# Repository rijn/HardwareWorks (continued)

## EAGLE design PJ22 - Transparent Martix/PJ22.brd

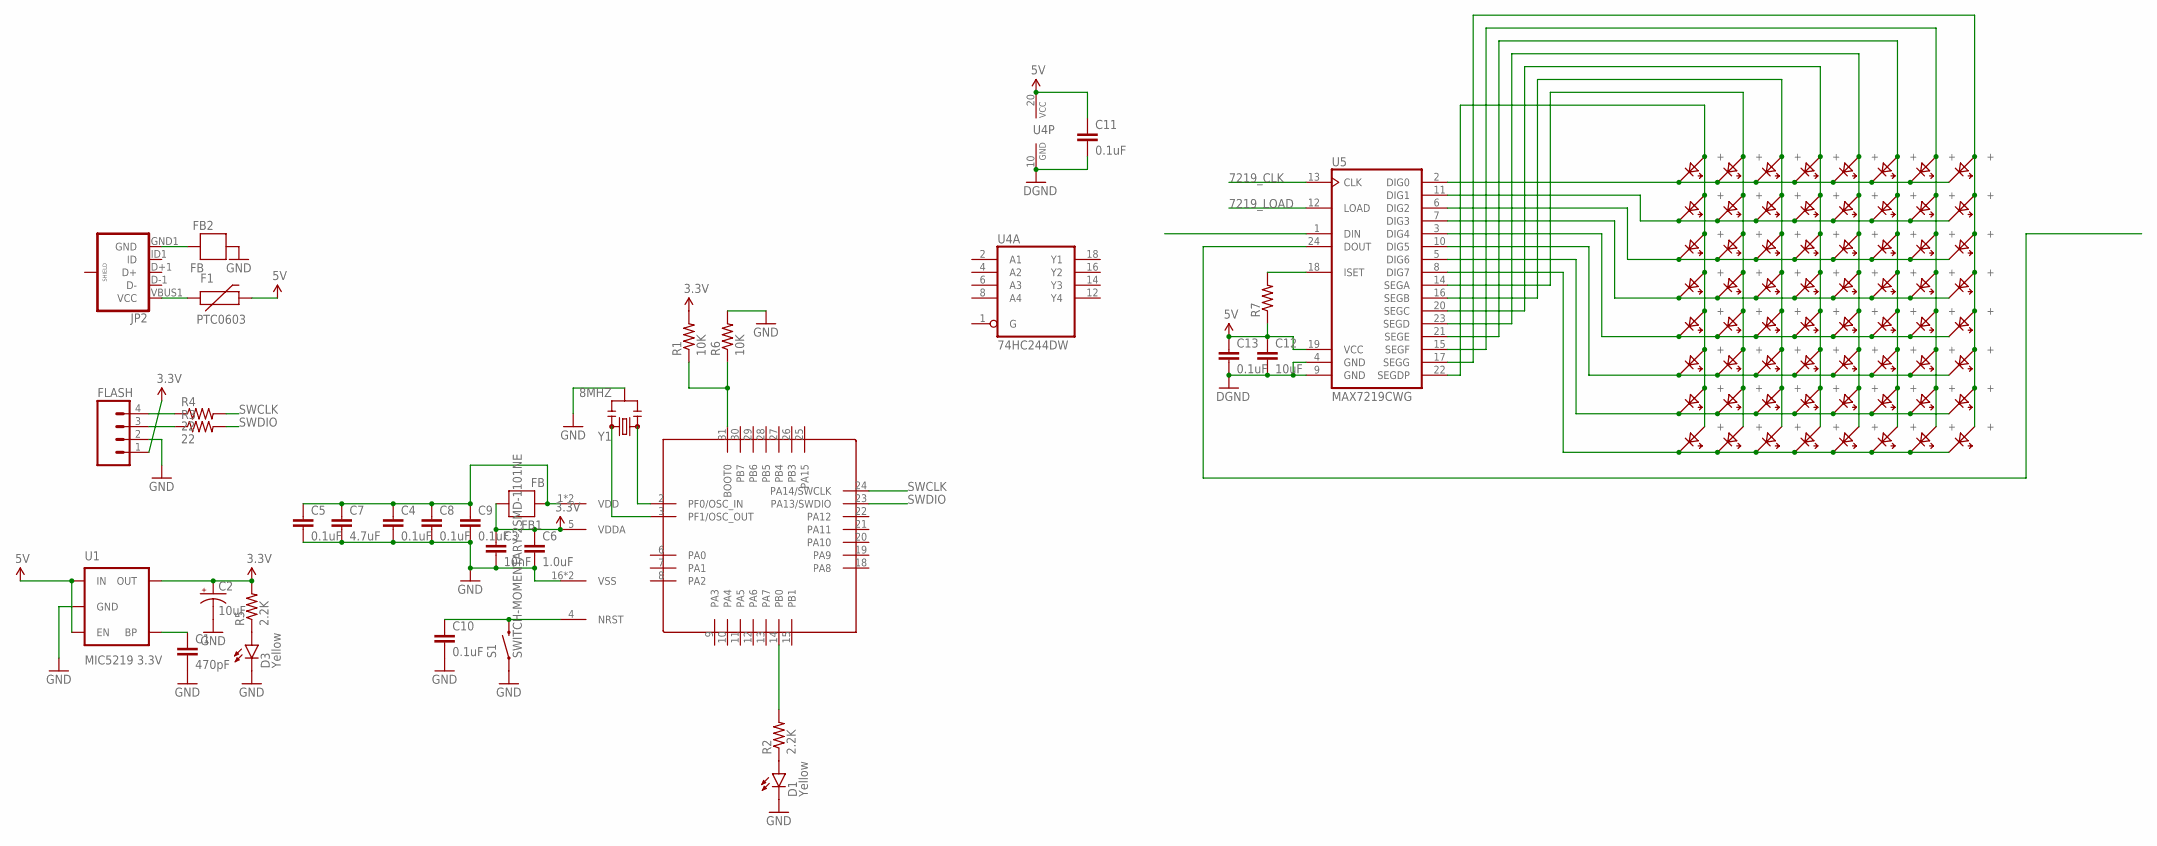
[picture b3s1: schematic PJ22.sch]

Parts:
C1: 470pF; 0402-CAP
C2: 10uF; EIA3216
C3: 10nF; 0402-CAP
C4, C5, C8, C9, C10: 0.1uF; 0402-CAP
C6: 1.0uF; 0603-CAP
C7: 4.7uF; 0603-CAP
C11, C13: 0.1uF; 0603-CAP
C12: 10uF; 1210
D1, D3: Yellow; LED-0603
DC1, DC2, DC3, DC4, DC5, DC6, DC7, DC8, DC9, DC10, DC11, DC12, DC13, DC14, DC15, DC16, DC17, DC18, DC19, DC20, DC21, DC22, DC23, DC24, DC25, DC26, DC27, DC28, DC29, DC30, DC31, DC32, DC33, DC34, DC35, DC36, DC37, DC38, DC39, DC40, DC41, DC42, DC43, DC44, DC45, DC46, DC47, DC48, DC49, DC50, DC51, DC52, DC53, DC54, DC55, DC56, DC57, DC58, DC59, DC60, DC61, DC62, DC63, DC64: LED_COMP
F1: PTC0603; 0603
FB1, FB2: FB; 0603
FLASH: M04SMD; 1X04-SMD
JP2: USB_MICROB_PLUGCONN-11752; USB-B-MICRO-SMD_V03
R1, R6: 10K; 0402-RES
R2, R5: 2.2K; 0402-RES
R3, R4: 22; 0402-RES
R7: RESISTOR0805-RES; 0805
S1: SWITCH-MOMENTARY-2SMD-1101NE; TACTILE-SWITCH-1101NE
U1: MIC5219 3.3V; SOT23-5
U2: STM32F030K6P6; LQFP32-0.8
U4: 74HC244DW; SO20W
U5: MAX7219CWG; SO24L
Y1: 8MHZ; RESONATOR-SMD

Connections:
3.3V: C2.A (+), C3.1, C6.1, FB1.1, FLASH.1, R1.2, R5.2, U1.5 (OUT), U2.5 (VDDA)
5V: C11.1, C12.1, C13.1, F1.2, R7.1, U1.1 (IN), U1.3 (EN), U4.20 (VCC), U5.19 (VCC)
7219_CLK: U5.13 (CLK)
7219_LOAD: U5.12 (LOAD)
COPOY: C1.2, C2.C (-), C3.2, C4.2, C5.2, C6.2, C7.2, C8.2, C9.2, C10.2, D1.C, D3.C, FB2.1, FLASH.2, R6.2, S1.1, U1.2 (GND), U2.16 (VSS), U2.32 (VSS), Y1.2
GND: C11.2, C12.2, C13.2, U4.10 (GND), U5.4 (GND), U5.9 (GND)
unnamed: C4.1, C5.1, C7.1, C8.1, C9.1, FB1.2, U2.1 (VDD), U2.17 (VDD)
unnamed: DC1.0603- (-), DC1.0805- (-), DC1.1206- (-), DC1.3528- (-), DC1.5050-1 (-), DC1.5050-3 (-), DC1.5050-5 (-), DC2.0603- (-), DC2.0805- (-), DC2.1206- (-), DC2.3528- (-), DC2.5050-1 (-), DC2.5050-3 (-), DC2.5050-5 (-), DC3.0603- (-), DC3.0805- (-), DC3.1206- (-), DC3.3528- (-), DC3.5050-1 (-), DC3.5050-3 (-), DC3.5050-5 (-), DC4.0603- (-), DC4.0805- (-), DC4.1206- (-), DC4.3528- (-), DC4.5050-1 (-), DC4.5050-3 (-), DC4.5050-5 (-), DC5.0603- (-), DC5.0805- (-), DC5.1206- (-), DC5.3528- (-), DC5.5050-1 (-), DC5.5050-3 (-), DC5.5050-5 (-), DC6.0603- (-), DC6.0805- (-), DC6.1206- (-), DC6.3528- (-), DC6.5050-1 (-), DC6.5050-3 (-), DC6.5050-5 (-), DC7.0603- (-), DC7.0805- (-), DC7.1206- (-), DC7.3528- (-), DC7.5050-1 (-), DC7.5050-3 (-), DC7.5050-5 (-), DC8.0603- (-), DC8.0805- (-), DC8.1206- (-), DC8.3528- (-), DC8.5050-1 (-), DC8.5050-3 (-), DC8.5050-5 (-), U5.2 (DIG0)
unnamed: C1.1, U1.4 (BP)
unnamed: FLASH.3, R3.1
unnamed: FLASH.4, R4.1
unnamed: DC9.0603- (-), DC9.0805- (-), DC9.1206- (-), DC9.3528- (-), DC9.5050-1 (-), DC9.5050-3 (-), DC9.5050-5 (-), DC10.0603- (-), DC10.0805- (-), DC10.1206- (-), DC10.3528- (-), DC10.5050-1 (-), DC10.5050-3 (-), DC10.5050-5 (-), DC11.0603- (-), DC11.0805- (-), DC11.1206- (-), DC11.3528- (-), DC11.5050-1 (-), DC11.5050-3 (-), DC11.5050-5 (-), DC12.0603- (-), DC12.0805- (-), DC12.1206- (-), DC12.3528- (-), DC12.5050-1 (-), DC12.5050-3 (-), DC12.5050-5 (-), DC13.0603- (-), DC13.0805- (-), DC13.1206- (-), DC13.3528- (-), DC13.5050-1 (-), DC13.5050-3 (-), DC13.5050-5 (-), DC14.0603- (-), DC14.0805- (-), DC14.1206- (-), DC14.3528- (-), DC14.5050-1 (-), DC14.5050-3 (-), DC14.5050-5 (-), DC15.0603- (-), DC15.0805- (-), DC15.1206- (-), DC15.3528- (-), DC15.5050-1 (-), DC15.5050-3 (-), DC15.5050-5 (-), DC16.0603- (-), DC16.0805- (-), DC16.1206- (-), DC16.3528- (-), DC16.5050-1 (-), DC16.5050-3 (-), DC16.5050-5 (-), U5.11 (DIG1)
unnamed: D1.A, R2.1
unnamed: DC1.0603+ (+), DC1.0805+ (+), DC1.1206+ (+), DC1.3528+ (+), DC1.5050-2 (+), DC1.5050-4 (+), DC1.5050-6 (+), DC9.0603+ (+), DC9.0805+ (+), DC9.1206+ (+), DC9.3528+ (+), DC9.5050-2 (+), DC9.5050-4 (+), DC9.5050-6 (+), DC17.0603+ (+), DC17.0805+ (+), DC17.1206+ (+), DC17.3528+ (+), DC17.5050-2 (+), DC17.5050-4 (+), DC17.5050-6 (+), DC25.0603+ (+), DC25.0805+ (+), DC25.1206+ (+), DC25.3528+ (+), DC25.5050-2 (+), DC25.5050-4 (+), DC25.5050-6 (+), DC33.0603+ (+), DC33.0805+ (+), DC33.1206+ (+), DC33.3528+ (+), DC33.5050-2 (+), DC33.5050-4 (+), DC33.5050-6 (+), DC41.0603+ (+), DC41.0805+ (+), DC41.1206+ (+), DC41.3528+ (+), DC41.5050-2 (+), DC41.5050-4 (+), DC41.5050-6 (+), DC49.0603+ (+), DC49.0805+ (+), DC49.1206+ (+), DC49.3528+ (+), DC49.5050-2 (+), DC49.5050-4 (+), DC49.5050-6 (+), DC57.0603+ (+), DC57.0805+ (+), DC57.1206+ (+), DC57.3528+ (+), DC57.5050-2 (+), DC57.5050-4 (+), DC57.5050-6 (+), U5.22 (SEGDP)
unnamed: R1.1, R6.1, U2.31 (BOOT0)
unnamed: DC2.0603+ (+), DC2.0805+ (+), DC2.1206+ (+), DC2.3528+ (+), DC2.5050-2 (+), DC2.5050-4 (+), DC2.5050-6 (+), DC10.0603+ (+), DC10.0805+ (+), DC10.1206+ (+), DC10.3528+ (+), DC10.5050-2 (+), DC10.5050-4 (+), DC10.5050-6 (+), DC18.0603+ (+), DC18.0805+ (+), DC18.1206+ (+), DC18.3528+ (+), DC18.5050-2 (+), DC18.5050-4 (+), DC18.5050-6 (+), DC26.0603+ (+), DC26.0805+ (+), DC26.1206+ (+), DC26.3528+ (+), DC26.5050-2 (+), DC26.5050-4 (+), DC26.5050-6 (+), DC34.0603+ (+), DC34.0805+ (+), DC34.1206+ (+), DC34.3528+ (+), DC34.5050-2 (+), DC34.5050-4 (+), DC34.5050-6 (+), DC42.0603+ (+), DC42.0805+ (+), DC42.1206+ (+), DC42.3528+ (+), DC42.5050-2 (+), DC42.5050-4 (+), DC42.5050-6 (+), DC50.0603+ (+), DC50.0805+ (+), DC50.1206+ (+), DC50.3528+ (+), DC50.5050-2 (+), DC50.5050-4 (+), DC50.5050-6 (+), DC58.0603+ (+), DC58.0805+ (+), DC58.1206+ (+), DC58.3528+ (+), DC58.5050-2 (+), DC58.5050-4 (+), DC58.5050-6 (+), U5.14 (SEGA)
unnamed: FB2.2, JP2.GND1 (GND)
unnamed: F1.1, JP2.VBUS1 (VCC)
unnamed: DC3.0603+ (+), DC3.0805+ (+), DC3.1206+ (+), DC3.3528+ (+), DC3.5050-2 (+), DC3.5050-4 (+), DC3.5050-6 (+), DC11.0603+ (+), DC11.0805+ (+), DC11.1206+ (+), DC11.3528+ (+), DC11.5050-2 (+), DC11.5050-4 (+), DC11.5050-6 (+), DC19.0603+ (+), DC19.0805+ (+), DC19.1206+ (+), DC19.3528+ (+), DC19.5050-2 (+), DC19.5050-4 (+), DC19.5050-6 (+), DC27.0603+ (+), DC27.0805+ (+), DC27.1206+ (+), DC27.3528+ (+), DC27.5050-2 (+), DC27.5050-4 (+), DC27.5050-6 (+), DC35.0603+ (+), DC35.0805+ (+), DC35.1206+ (+), DC35.3528+ (+), DC35.5050-2 (+), DC35.5050-4 (+), DC35.5050-6 (+), DC43.0603+ (+), DC43.0805+ (+), DC43.1206+ (+), DC43.3528+ (+), DC43.5050-2 (+), DC43.5050-4 (+), DC43.5050-6 (+), DC51.0603+ (+), DC51.0805+ (+), DC51.1206+ (+), DC51.3528+ (+), DC51.5050-2 (+), DC51.5050-4 (+), DC51.5050-6 (+), DC59.0603+ (+), DC59.0805+ (+), DC59.1206+ (+), DC59.3528+ (+), DC59.5050-2 (+), DC59.5050-4 (+), DC59.5050-6 (+), U5.16 (SEGB)
unnamed: DC4.0603+ (+), DC4.0805+ (+), DC4.1206+ (+), DC4.3528+ (+), DC4.5050-2 (+), DC4.5050-4 (+), DC4.5050-6 (+), DC12.0603+ (+), DC12.0805+ (+), DC12.1206+ (+), DC12.3528+ (+), DC12.5050-2 (+), DC12.5050-4 (+), DC12.5050-6 (+), DC20.0603+ (+), DC20.0805+ (+), DC20.1206+ (+), DC20.3528+ (+), DC20.5050-2 (+), DC20.5050-4 (+), DC20.5050-6 (+), DC28.0603+ (+), DC28.0805+ (+), DC28.1206+ (+), DC28.3528+ (+), DC28.5050-2 (+), DC28.5050-4 (+), DC28.5050-6 (+), DC36.0603+ (+), DC36.0805+ (+), DC36.1206+ (+), DC36.3528+ (+), DC36.5050-2 (+), DC36.5050-4 (+), DC36.5050-6 (+), DC44.0603+ (+), DC44.0805+ (+), DC44.1206+ (+), DC44.3528+ (+), DC44.5050-2 (+), DC44.5050-4 (+), DC44.5050-6 (+), DC52.0603+ (+), DC52.0805+ (+), DC52.1206+ (+), DC52.3528+ (+), DC52.5050-2 (+), DC52.5050-4 (+), DC52.5050-6 (+), DC60.0603+ (+), DC60.0805+ (+), DC60.1206+ (+), DC60.3528+ (+), DC60.5050-2 (+), DC60.5050-4 (+), DC60.5050-6 (+), U5.20 (SEGC)
unnamed: DC5.0603+ (+), DC5.0805+ (+), DC5.1206+ (+), DC5.3528+ (+), DC5.5050-2 (+), DC5.5050-4 (+), DC5.5050-6 (+), DC13.0603+ (+), DC13.0805+ (+), DC13.1206+ (+), DC13.3528+ (+), DC13.5050-2 (+), DC13.5050-4 (+), DC13.5050-6 (+), DC21.0603+ (+), DC21.0805+ (+), DC21.1206+ (+), DC21.3528+ (+), DC21.5050-2 (+), DC21.5050-4 (+), DC21.5050-6 (+), DC29.0603+ (+), DC29.0805+ (+), DC29.1206+ (+), DC29.3528+ (+), DC29.5050-2 (+), DC29.5050-4 (+), DC29.5050-6 (+), DC37.0603+ (+), DC37.0805+ (+), DC37.1206+ (+), DC37.3528+ (+), DC37.5050-2 (+), DC37.5050-4 (+), DC37.5050-6 (+), DC45.0603+ (+), DC45.0805+ (+), DC45.1206+ (+), DC45.3528+ (+), DC45.5050-2 (+), DC45.5050-4 (+), DC45.5050-6 (+), DC53.0603+ (+), DC53.0805+ (+), DC53.1206+ (+), DC53.3528+ (+), DC53.5050-2 (+), DC53.5050-4 (+), DC53.5050-6 (+), DC61.0603+ (+), DC61.0805+ (+), DC61.1206+ (+), DC61.3528+ (+), DC61.5050-2 (+), DC61.5050-4 (+), DC61.5050-6 (+), U5.23 (SEGD)
unnamed: DC6.0603+ (+), DC6.0805+ (+), DC6.1206+ (+), DC6.3528+ (+), DC6.5050-2 (+), DC6.5050-4 (+), DC6.5050-6 (+), DC14.0603+ (+), DC14.0805+ (+), DC14.1206+ (+), DC14.3528+ (+), DC14.5050-2 (+), DC14.5050-4 (+), DC14.5050-6 (+), DC22.0603+ (+), DC22.0805+ (+), DC22.1206+ (+), DC22.3528+ (+), DC22.5050-2 (+), DC22.5050-4 (+), DC22.5050-6 (+), DC30.0603+ (+), DC30.0805+ (+), DC30.1206+ (+), DC30.3528+ (+), DC30.5050-2 (+), DC30.5050-4 (+), DC30.5050-6 (+), DC38.0603+ (+), DC38.0805+ (+), DC38.1206+ (+), DC38.3528+ (+), DC38.5050-2 (+), DC38.5050-4 (+), DC38.5050-6 (+), DC46.0603+ (+), DC46.0805+ (+), DC46.1206+ (+), DC46.3528+ (+), DC46.5050-2 (+), DC46.5050-4 (+), DC46.5050-6 (+), DC54.0603+ (+), DC54.0805+ (+), DC54.1206+ (+), DC54.3528+ (+), DC54.5050-2 (+), DC54.5050-4 (+), DC54.5050-6 (+), DC62.0603+ (+), DC62.0805+ (+), DC62.1206+ (+), DC62.3528+ (+), DC62.5050-2 (+), DC62.5050-4 (+), DC62.5050-6 (+), U5.21 (SEGE)
unnamed: DC7.0603+ (+), DC7.0805+ (+), DC7.1206+ (+), DC7.3528+ (+), DC7.5050-2 (+), DC7.5050-4 (+), DC7.5050-6 (+), DC15.0603+ (+), DC15.0805+ (+), DC15.1206+ (+), DC15.3528+ (+), DC15.5050-2 (+), DC15.5050-4 (+), DC15.5050-6 (+), DC23.0603+ (+), DC23.0805+ (+), DC23.1206+ (+), DC23.3528+ (+), DC23.5050-2 (+), DC23.5050-4 (+), DC23.5050-6 (+), DC31.0603+ (+), DC31.0805+ (+), DC31.1206+ (+), DC31.3528+ (+), DC31.5050-2 (+), DC31.5050-4 (+), DC31.5050-6 (+), DC39.0603+ (+), DC39.0805+ (+), DC39.1206+ (+), DC39.3528+ (+), DC39.5050-2 (+), DC39.5050-4 (+), DC39.5050-6 (+), DC47.0603+ (+), DC47.0805+ (+), DC47.1206+ (+), DC47.3528+ (+), DC47.5050-2 (+), DC47.5050-4 (+), DC47.5050-6 (+), DC55.0603+ (+), DC55.0805+ (+), DC55.1206+ (+), DC55.3528+ (+), DC55.5050-2 (+), DC55.5050-4 (+), DC55.5050-6 (+), DC63.0603+ (+), DC63.0805+ (+), DC63.1206+ (+), DC63.3528+ (+), DC63.5050-2 (+), DC63.5050-4 (+), DC63.5050-6 (+), U5.15 (SEGF)
unnamed: DC8.0603+ (+), DC8.0805+ (+), DC8.1206+ (+), DC8.3528+ (+), DC8.5050-2 (+), DC8.5050-4 (+), DC8.5050-6 (+), DC16.0603+ (+), DC16.0805+ (+), DC16.1206+ (+), DC16.3528+ (+), DC16.5050-2 (+), DC16.5050-4 (+), DC16.5050-6 (+), DC24.0603+ (+), DC24.0805+ (+), DC24.1206+ (+), DC24.3528+ (+), DC24.5050-2 (+), DC24.5050-4 (+), DC24.5050-6 (+), DC32.0603+ (+), DC32.0805+ (+), DC32.1206+ (+), DC32.3528+ (+), DC32.5050-2 (+), DC32.5050-4 (+), DC32.5050-6 (+), DC40.0603+ (+), DC40.0805+ (+), DC40.1206+ (+), DC40.3528+ (+), DC40.5050-2 (+), DC40.5050-4 (+), DC40.5050-6 (+), DC48.0603+ (+), DC48.0805+ (+), DC48.1206+ (+), DC48.3528+ (+), DC48.5050-2 (+), DC48.5050-4 (+), DC48.5050-6 (+), DC56.0603+ (+), DC56.0805+ (+), DC56.1206+ (+), DC56.3528+ (+), DC56.5050-2 (+), DC56.5050-4 (+), DC56.5050-6 (+), DC64.0603+ (+), DC64.0805+ (+), DC64.1206+ (+), DC64.3528+ (+), DC64.5050-2 (+), DC64.5050-4 (+), DC64.5050-6 (+), U5.17 (SEGG)
unnamed: DC17.0603- (-), DC17.0805- (-), DC17.1206- (-), DC17.3528- (-), DC17.5050-1 (-), DC17.5050-3 (-), DC17.5050-5 (-), DC18.0603- (-), DC18.0805- (-), DC18.1206- (-), DC18.3528- (-), DC18.5050-1 (-), DC18.5050-3 (-), DC18.5050-5 (-), DC19.0603- (-), DC19.0805- (-), DC19.1206- (-), DC19.3528- (-), DC19.5050-1 (-), DC19.5050-3 (-), DC19.5050-5 (-), DC20.0603- (-), DC20.0805- (-), DC20.1206- (-), DC20.3528- (-), DC20.5050-1 (-), DC20.5050-3 (-), DC20.5050-5 (-), DC21.0603- (-), DC21.0805- (-), DC21.1206- (-), DC21.3528- (-), DC21.5050-1 (-), DC21.5050-3 (-), DC21.5050-5 (-), DC22.0603- (-), DC22.0805- (-), DC22.1206- (-), DC22.3528- (-), DC22.5050-1 (-), DC22.5050-3 (-), DC22.5050-5 (-), DC23.0603- (-), DC23.0805- (-), DC23.1206- (-), DC23.3528- (-), DC23.5050-1 (-), DC23.5050-3 (-), DC23.5050-5 (-), DC24.0603- (-), DC24.0805- (-), DC24.1206- (-), DC24.3528- (-), DC24.5050-1 (-), DC24.5050-3 (-), DC24.5050-5 (-), U5.6 (DIG2)
unnamed: DC25.0603- (-), DC25.0805- (-), DC25.1206- (-), DC25.3528- (-), DC25.5050-1 (-), DC25.5050-3 (-), DC25.5050-5 (-), DC26.0603- (-), DC26.0805- (-), DC26.1206- (-), DC26.3528- (-), DC26.5050-1 (-), DC26.5050-3 (-), DC26.5050-5 (-), DC27.0603- (-), DC27.0805- (-), DC27.1206- (-), DC27.3528- (-), DC27.5050-1 (-), DC27.5050-3 (-), DC27.5050-5 (-), DC28.0603- (-), DC28.0805- (-), DC28.1206- (-), DC28.3528- (-), DC28.5050-1 (-), DC28.5050-3 (-), DC28.5050-5 (-), DC29.0603- (-), DC29.0805- (-), DC29.1206- (-), DC29.3528- (-), DC29.5050-1 (-), DC29.5050-3 (-), DC29.5050-5 (-), DC30.0603- (-), DC30.0805- (-), DC30.1206- (-), DC30.3528- (-), DC30.5050-1 (-), DC30.5050-3 (-), DC30.5050-5 (-), DC31.0603- (-), DC31.0805- (-), DC31.1206- (-), DC31.3528- (-), DC31.5050-1 (-), DC31.5050-3 (-), DC31.5050-5 (-), DC32.0603- (-), DC32.0805- (-), DC32.1206- (-), DC32.3528- (-), DC32.5050-1 (-), DC32.5050-3 (-), DC32.5050-5 (-), U5.7 (DIG3)
unnamed: DC33.0603- (-), DC33.0805- (-), DC33.1206- (-), DC33.3528- (-), DC33.5050-1 (-), DC33.5050-3 (-), DC33.5050-5 (-), DC34.0603- (-), DC34.0805- (-), DC34.1206- (-), DC34.3528- (-), DC34.5050-1 (-), DC34.5050-3 (-), DC34.5050-5 (-), DC35.0603- (-), DC35.0805- (-), DC35.1206- (-), DC35.3528- (-), DC35.5050-1 (-), DC35.5050-3 (-), DC35.5050-5 (-), DC36.0603- (-), DC36.0805- (-), DC36.1206- (-), DC36.3528- (-), DC36.5050-1 (-), DC36.5050-3 (-), DC36.5050-5 (-), DC37.0603- (-), DC37.0805- (-), DC37.1206- (-), DC37.3528- (-), DC37.5050-1 (-), DC37.5050-3 (-), DC37.5050-5 (-), DC38.0603- (-), DC38.0805- (-), DC38.1206- (-), DC38.3528- (-), DC38.5050-1 (-), DC38.5050-3 (-), DC38.5050-5 (-), DC39.0603- (-), DC39.0805- (-), DC39.1206- (-), DC39.3528- (-), DC39.5050-1 (-), DC39.5050-3 (-), DC39.5050-5 (-), DC40.0603- (-), DC40.0805- (-), DC40.1206- (-), DC40.3528- (-), DC40.5050-1 (-), DC40.5050-3 (-), DC40.5050-5 (-), U5.3 (DIG4)
unnamed: DC41.0603- (-), DC41.0805- (-), DC41.1206- (-), DC41.3528- (-), DC41.5050-1 (-), DC41.5050-3 (-), DC41.5050-5 (-), DC42.0603- (-), DC42.0805- (-), DC42.1206- (-), DC42.3528- (-), DC42.5050-1 (-), DC42.5050-3 (-), DC42.5050-5 (-), DC43.0603- (-), DC43.0805- (-), DC43.1206- (-), DC43.3528- (-), DC43.5050-1 (-), DC43.5050-3 (-), DC43.5050-5 (-), DC44.0603- (-), DC44.0805- (-), DC44.1206- (-), DC44.3528- (-), DC44.5050-1 (-), DC44.5050-3 (-), DC44.5050-5 (-), DC45.0603- (-), DC45.0805- (-), DC45.1206- (-), DC45.3528- (-), DC45.5050-1 (-), DC45.5050-3 (-), DC45.5050-5 (-), DC46.0603- (-), DC46.0805- (-), DC46.1206- (-), DC46.3528- (-), DC46.5050-1 (-), DC46.5050-3 (-), DC46.5050-5 (-), DC47.0603- (-), DC47.0805- (-), DC47.1206- (-), DC47.3528- (-), DC47.5050-1 (-), DC47.5050-3 (-), DC47.5050-5 (-), DC48.0603- (-), DC48.0805- (-), DC48.1206- (-), DC48.3528- (-), DC48.5050-1 (-), DC48.5050-3 (-), DC48.5050-5 (-), U5.10 (DIG5)
unnamed: DC49.0603- (-), DC49.0805- (-), DC49.1206- (-), DC49.3528- (-), DC49.5050-1 (-), DC49.5050-3 (-), DC49.5050-5 (-), DC50.0603- (-), DC50.0805- (-), DC50.1206- (-), DC50.3528- (-), DC50.5050-1 (-), DC50.5050-3 (-), DC50.5050-5 (-), DC51.0603- (-), DC51.0805- (-), DC51.1206- (-), DC51.3528- (-), DC51.5050-1 (-), DC51.5050-3 (-), DC51.5050-5 (-), DC52.0603- (-), DC52.0805- (-), DC52.1206- (-), DC52.3528- (-), DC52.5050-1 (-), DC52.5050-3 (-), DC52.5050-5 (-), DC53.0603- (-), DC53.0805- (-), DC53.1206- (-), DC53.3528- (-), DC53.5050-1 (-), DC53.5050-3 (-), DC53.5050-5 (-), DC54.0603- (-), DC54.0805- (-), DC54.1206- (-), DC54.3528- (-), DC54.5050-1 (-), DC54.5050-3 (-), DC54.5050-5 (-), DC55.0603- (-), DC55.0805- (-), DC55.1206- (-), DC55.3528- (-), DC55.5050-1 (-), DC55.5050-3 (-), DC55.5050-5 (-), DC56.0603- (-), DC56.0805- (-), DC56.1206- (-), DC56.3528- (-), DC56.5050-1 (-), DC56.5050-3 (-), DC56.5050-5 (-), U5.5 (DIG6)
unnamed: DC57.0603- (-), DC57.0805- (-), DC57.1206- (-), DC57.3528- (-), DC57.5050-1 (-), DC57.5050-3 (-), DC57.5050-5 (-), DC58.0603- (-), DC58.0805- (-), DC58.1206- (-), DC58.3528- (-), DC58.5050-1 (-), DC58.5050-3 (-), DC58.5050-5 (-), DC59.0603- (-), DC59.0805- (-), DC59.1206- (-), DC59.3528- (-), DC59.5050-1 (-), DC59.5050-3 (-), DC59.5050-5 (-), DC60.0603- (-), DC60.0805- (-), DC60.1206- (-), DC60.3528- (-), DC60.5050-1 (-), DC60.5050-3 (-), DC60.5050-5 (-), DC61.0603- (-), DC61.0805- (-), DC61.1206- (-), DC61.3528- (-), DC61.5050-1 (-), DC61.5050-3 (-), DC61.5050-5 (-), DC62.0603- (-), DC62.0805- (-), DC62.1206- (-), DC62.3528- (-), DC62.5050-1 (-), DC62.5050-3 (-), DC62.5050-5 (-), DC63.0603- (-), DC63.0805- (-), DC63.1206- (-), DC63.3528- (-), DC63.5050-1 (-), DC63.5050-3 (-), DC63.5050-5 (-), DC64.0603- (-), DC64.0805- (-), DC64.1206- (-), DC64.3528- (-), DC64.5050-1 (-), DC64.5050-3 (-), DC64.5050-5 (-), U5.8 (DIG7)
unnamed: R7.2, U5.18 (ISET)
unnamed: D3.A, R5.1
NRST: C10.1, S1.2, U2.4 (NRST)
PB0: R2.2, U2.14 (PB0)
PF0: U2.2 (PF0/OSC_IN), Y1.1
PF1: U2.3 (PF1/OSC_OUT), Y1.3
SWCLK: R4.2, U2.24 (PA14/SWCLK)
SWDIO: R3.2, U2.23 (PA13/SWDIO)

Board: 2 copper layers, 97 parts (0 on the bottom side), 36 nets, no tracks yet.

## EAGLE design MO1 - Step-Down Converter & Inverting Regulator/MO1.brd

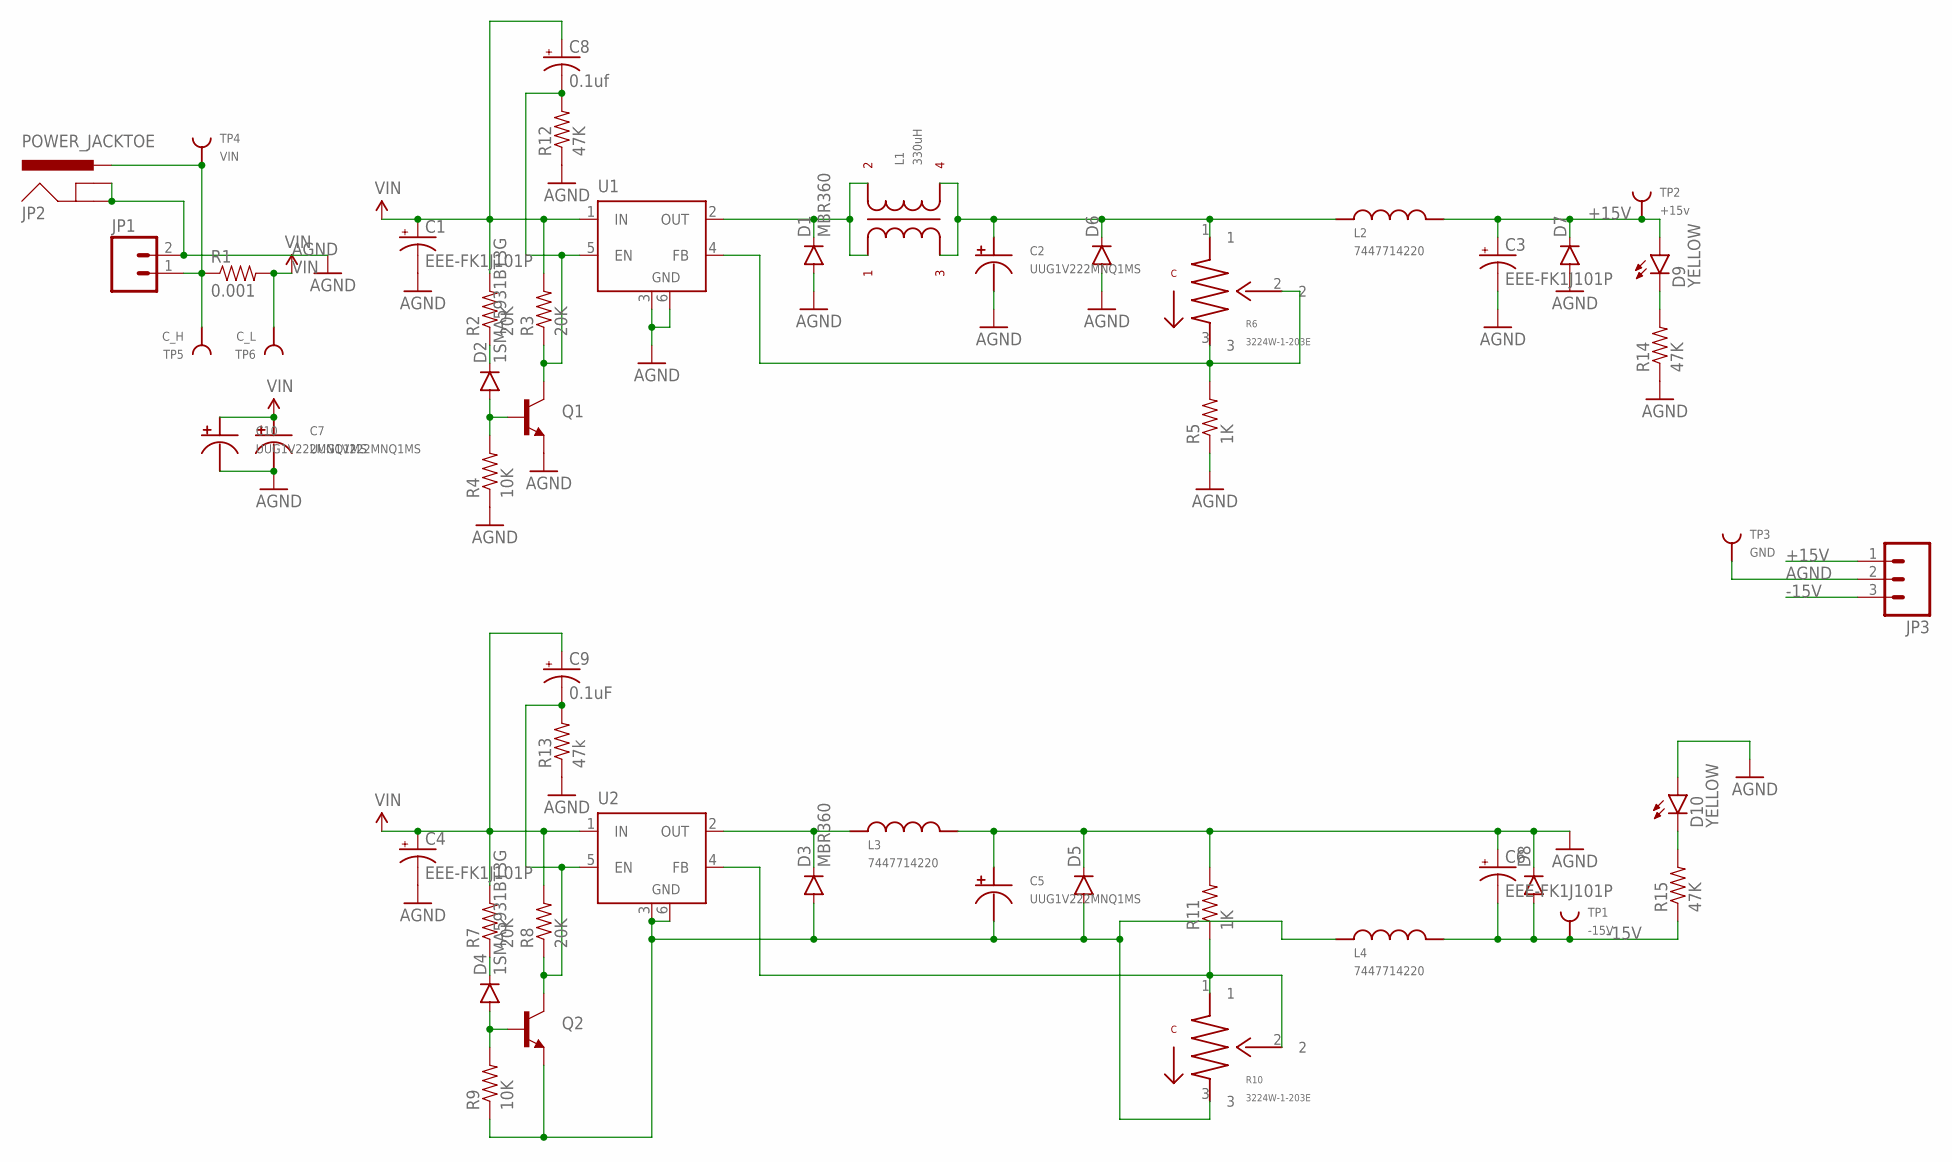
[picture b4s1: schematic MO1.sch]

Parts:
C1, C3, C4, C6: EEE-FK1J101P; PANASONIC_G
C2, C5, C7, C10: UUG1V222MNQ1MS; POL_18X21.5
C8: 0.1uf; PANASONIC_C
C9: 0.1uF; PANASONIC_C
D1, D3: MBR360; SMB-DIODE
D2, D4: 1SMA5931BT3G; SMA-DIODE
D5, D6, D7, D8: DIODESMA; SMA-DIODE
D9, D10: YELLOW; LED-1206
JP1: M023.5MM_LOCK; SCREWTERMINAL-3.5MM-2_LOCK
JP2: POWER_JACKTOE; POWER_JACK_SMD_OVERPASTE_TOE
JP3: M03SCREW_LOCK; SCREWTERMINAL-3.5MM-3_LOCK.007S
L1: 330uH; DRQ127
L2, L3, L4: 7447714220; INDUCTOR_10X10
Q1, Q2: TRANSISTOR_NPNSOT23-3; SOT23-3
R1: 0.001; 2512
R2, R3, R7, R8: 20K; 0603-RES
R4, R9: 10K; 0603-RES
R5, R11: 1K; 0805
R6, R10: 3224W-1-203E; 3224W
R12, R14, R15: 47K; 0603-RES
R13: 47k; 0603-RES
TP1: -15V; TP
TP2: +15v; TP
TP3: GND; TP
TP4: VIN; TP
TP5: C_H; TP
TP6: C_L; TP
U1, U2: LM2596S; TO263-5

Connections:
+15V: C3.+, D7.C, D9.A, JP3.1, L2.2, TP2.P$1
-15V: C6.-, D8.A, JP3.3, L4.2, R15.1, TP1.P$1
AGND: C1.-, C2.NEGATIVE, C3.-, C4.-, C5.POSITIVE, C6.+, C7.NEGATIVE, C10.NEGATIVE, D1.A, D5.C, D6.A, D7.A, D8.C, D10.A, JP1.2, JP2.GND (GNDBREAK), JP2.P$4 (GND), JP3.2, L3.2, Q1.2 (E), R4.1, R5.1, R11.2, R12.1, R13.1, R14.1, TP3.P$1, U1.3 (GND), U1.6 (GND)
unnamed: JP1.1, JP2.VIN0 (PWR), R1.1, TP4.P$1, TP5.P$1
unnamed: C2.POSITIVE, D6.C, L1.3, L1.4, L2.1, R6.1
unnamed: D1.C, L1.1, L1.2, U1.2 (OUT)
unnamed: D2.C, R2.1
unnamed: D2.A, Q1.1 (B), R4.2
unnamed: D9.C, R14.2
unnamed: R5.2, R6.2, R6.3, U1.4 (FB)
unnamed: D3.C, L3.1, U2.2 (OUT)
unnamed: C5.NEGATIVE, D3.A, D5.A, L4.1, Q2.2 (E), R9.1, R10.3, U2.3 (GND), U2.6 (GND)
unnamed: D4.C, R7.1
unnamed: D4.A, Q2.1 (B), R9.2
unnamed: D10.C, R15.2
unnamed: R10.1, R10.2, R11.1, U2.4 (FB)
unnamed: C8.-, Q1.3 (C), R3.1, R12.2, U1.5 (EN)
unnamed: C9.-, Q2.3 (C), R8.1, R13.2, U2.5 (EN)
VIN: C1.+, C4.+, C7.POSITIVE, C8.+, C9.+, C10.POSITIVE, R1.2, R2.2, R3.2, R7.2, R8.2, TP6.P$1, U1.1 (IN), U2.1 (IN)

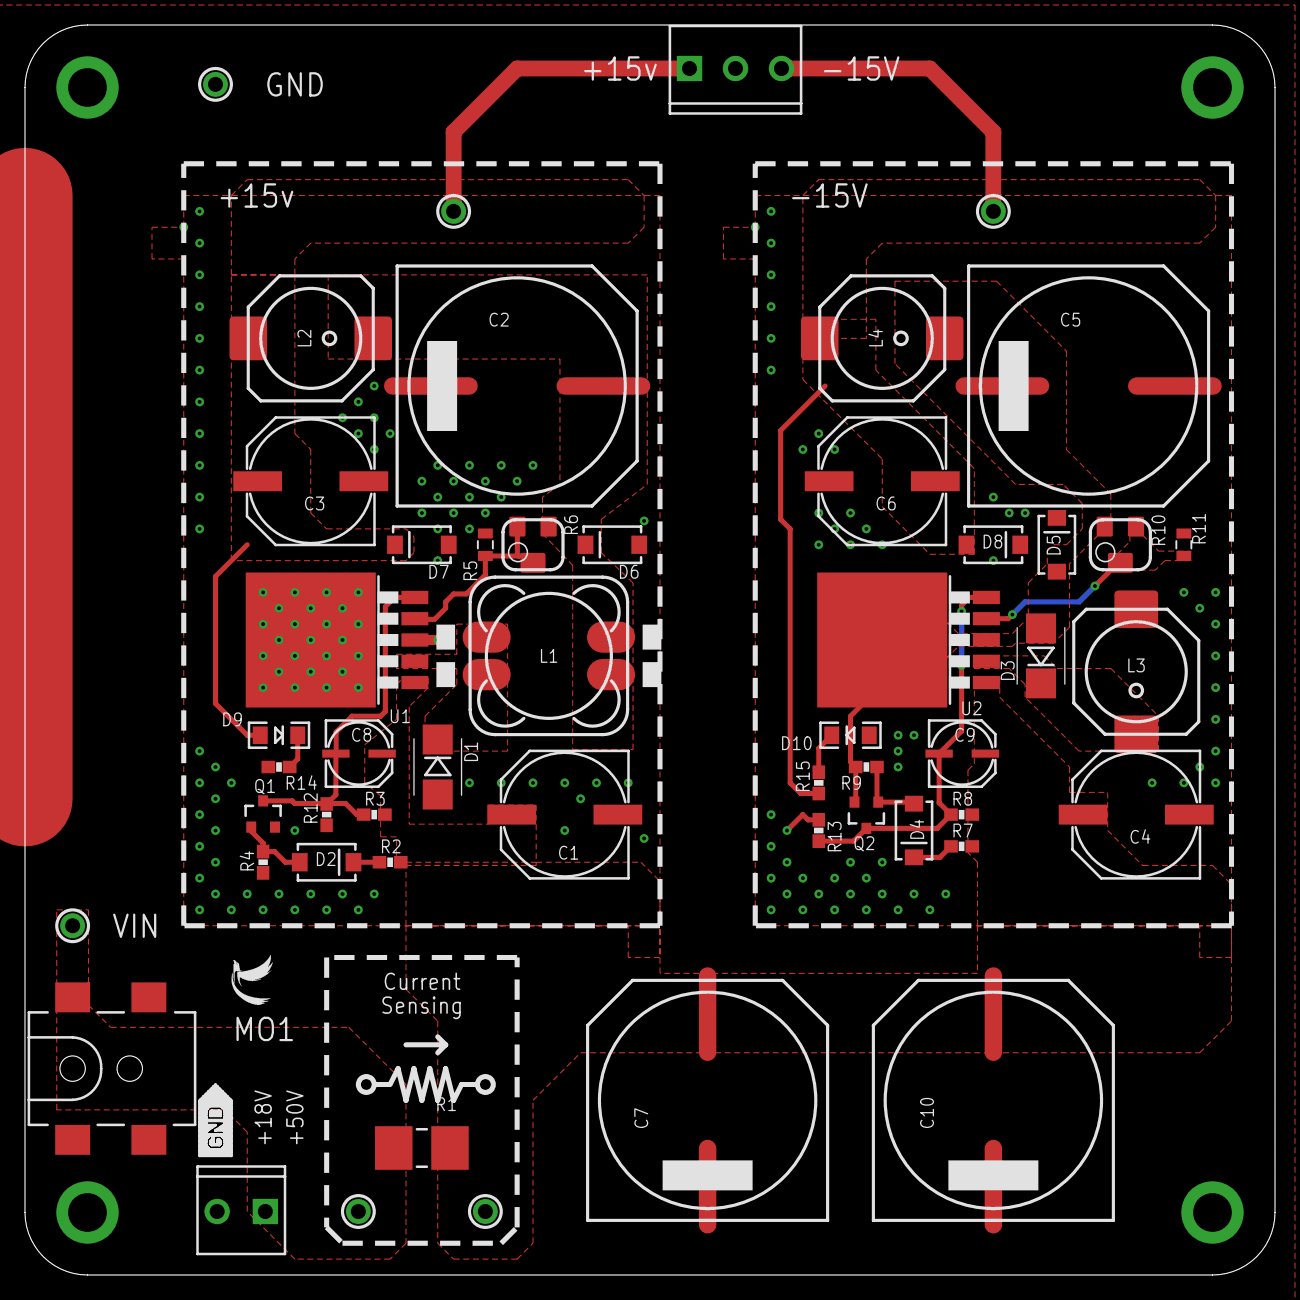
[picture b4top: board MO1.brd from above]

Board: 2 copper layers, 100.0 x 100.0 mm, 53 parts (0 on the bottom side), 19 nets.

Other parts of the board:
U$19: LOGO

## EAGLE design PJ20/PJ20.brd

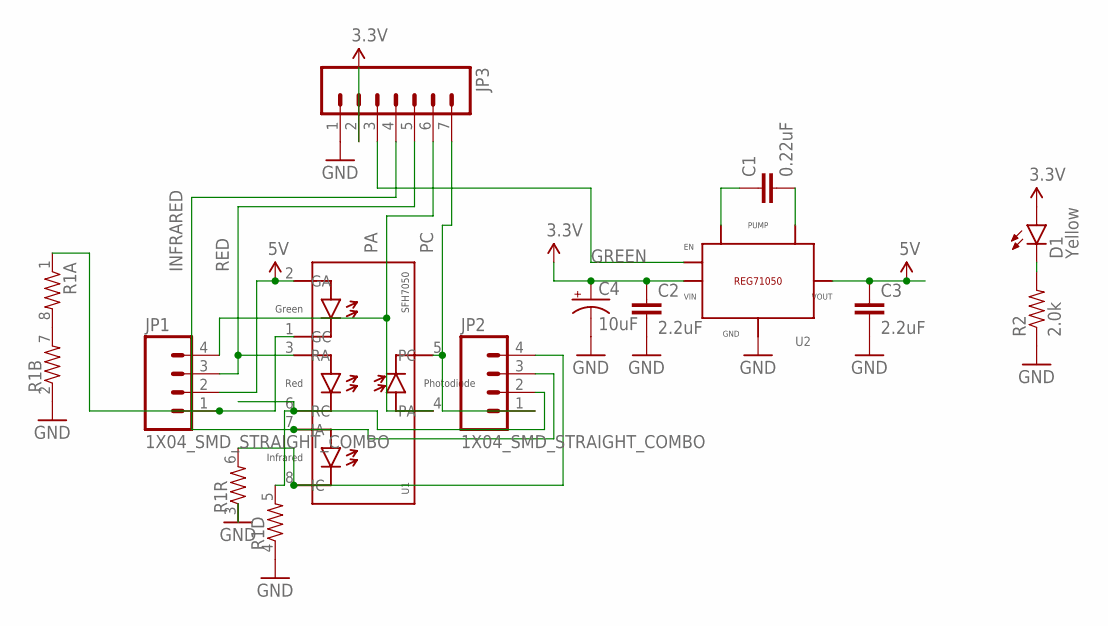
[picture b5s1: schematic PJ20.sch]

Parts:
C1: 0.22uF; 0603-CAP
C2, C3: 2.2uF; 0805-CAP
C4: 10uF; EIA3216
D1: Yellow; LED-0603
JP1, JP2: 1X04_SMD_STRAIGHT_COMBO
JP3: M07LOCK; 1X07_LOCK
R1: RESISTOR-ARRAY0603-ARV; 0603-ARV
R2: 2.0k; 0603-RES
U1: SFH7050
U2: REG71050; DDC

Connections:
3.3V: C2.1, C4.A (+), D1.A, JP3.2, U2.5 (VIN)
5V: C3.1, JP1.2, U1.2 (GA), U2.1 (VOUT)
GND: C2.2, C3.2, C4.C (-), JP3.1, R1.2 (1), R1.3 (1), R1.4 (1), R2.1, U2.2 (GND)
GREEN: JP3.3, U2.3 (ENABLE)
INFRARED: JP2.3, JP3.4, U1.7 (IA)
unnamed: JP1.1, R1.1, U1.1 (GC)
unnamed: D1.C, R2.2
unnamed: C1.1, U2.4 (CPUMP-)
unnamed: C1.2, U2.6 (CPUMP+)
unnamed: JP2.2, R1.5 (2), U1.6 (RC)
unnamed: JP2.4, R1.6 (2), U1.8 (IC)
unnamed: R1.7 (2), R1.8 (2)
PA: JP1.4, JP3.6, U1.4 (PA)
PC: JP2.1, JP3.7, U1.5 (PC)
RED: JP1.3, JP3.5, U1.3 (RA)

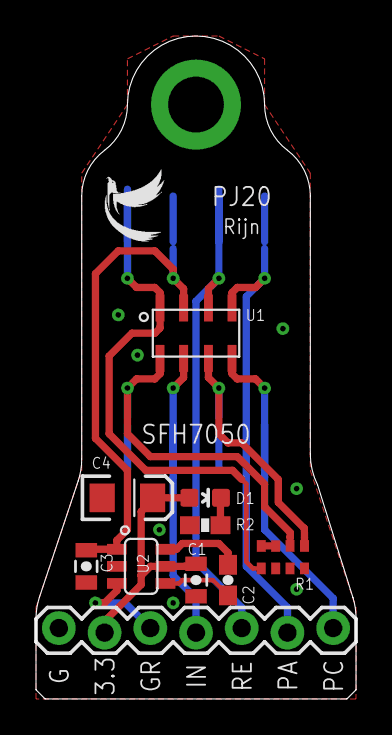
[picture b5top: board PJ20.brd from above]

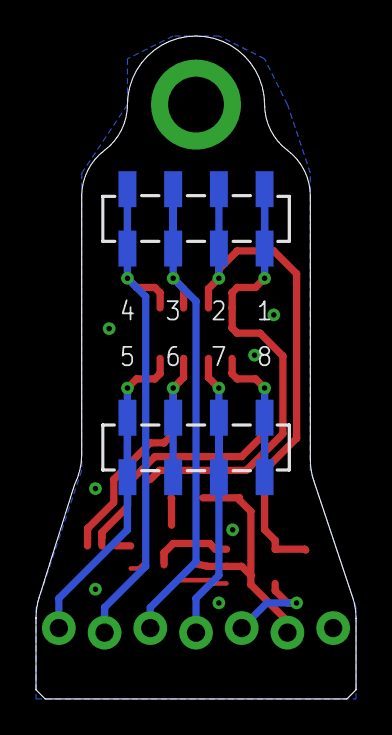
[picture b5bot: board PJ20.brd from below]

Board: 2 copper layers, 17.8 x 36.8 mm, 13 parts (2 on the bottom side), 15 nets.

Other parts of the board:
U$1: LOGO

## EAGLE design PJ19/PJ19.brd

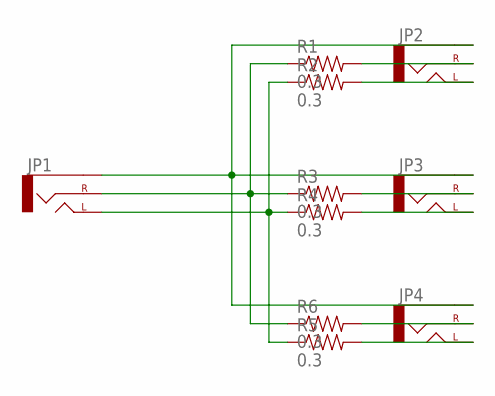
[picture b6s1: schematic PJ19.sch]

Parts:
JP1, JP2, JP3, JP4: AUDIO-JACKPTH; AUDIO-JACK
R1, R2, R3, R4, R5, R6: 0.3; 0805

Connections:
GND: JP1.SLEEVE, JP2.SLEEVE, JP3.SLEEVE, JP4.SLEEVE
unnamed: JP1.TIP (LEFT), R2.1, R4.1, R5.1
unnamed: JP3.TIP (LEFT), R4.2
unnamed: JP2.TIP (LEFT), R2.2
unnamed: JP3.RING (RIGHT), R3.2
unnamed: JP2.RING (RIGHT), R1.2
unnamed: JP1.RING (RIGHT), R1.1, R3.1, R6.1
unnamed: JP4.RING (RIGHT), R6.2
unnamed: JP4.TIP (LEFT), R5.2

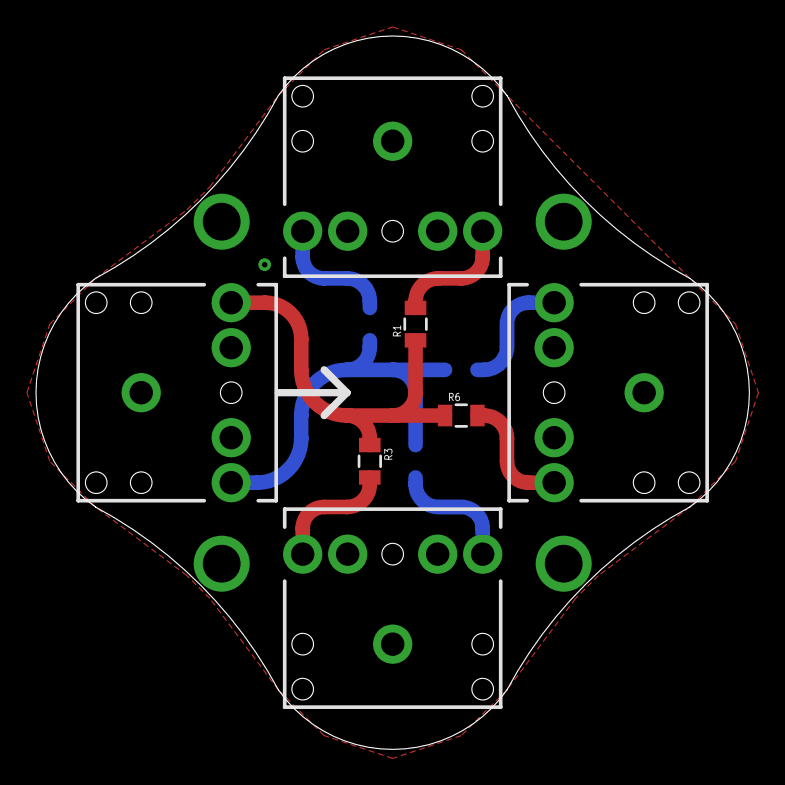
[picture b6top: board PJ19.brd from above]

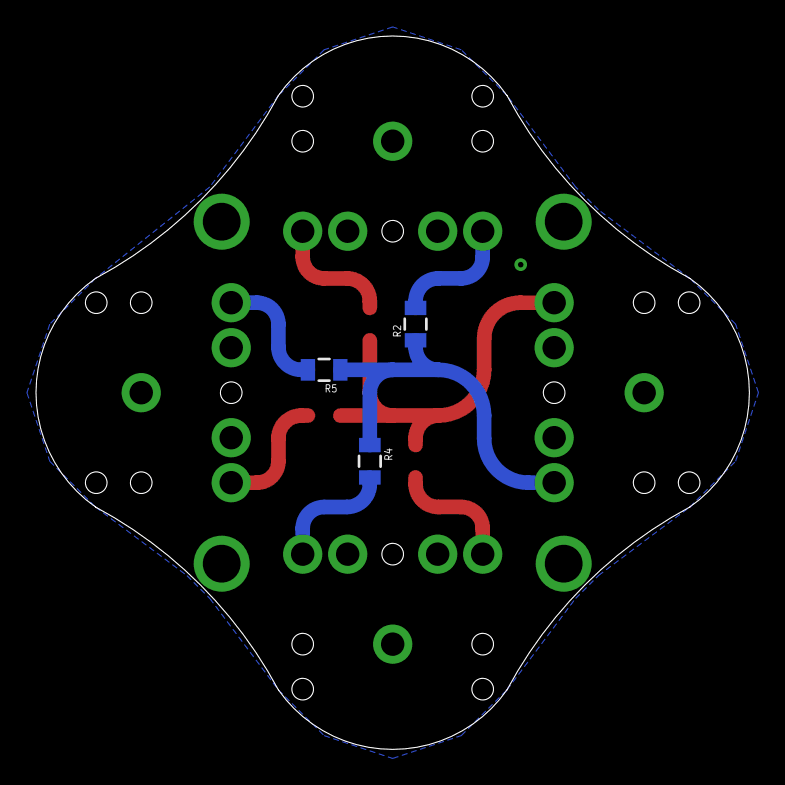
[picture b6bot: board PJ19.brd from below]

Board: 2 copper layers, 39.6 x 39.6 mm, 10 parts (3 on the bottom side), 9 nets.
